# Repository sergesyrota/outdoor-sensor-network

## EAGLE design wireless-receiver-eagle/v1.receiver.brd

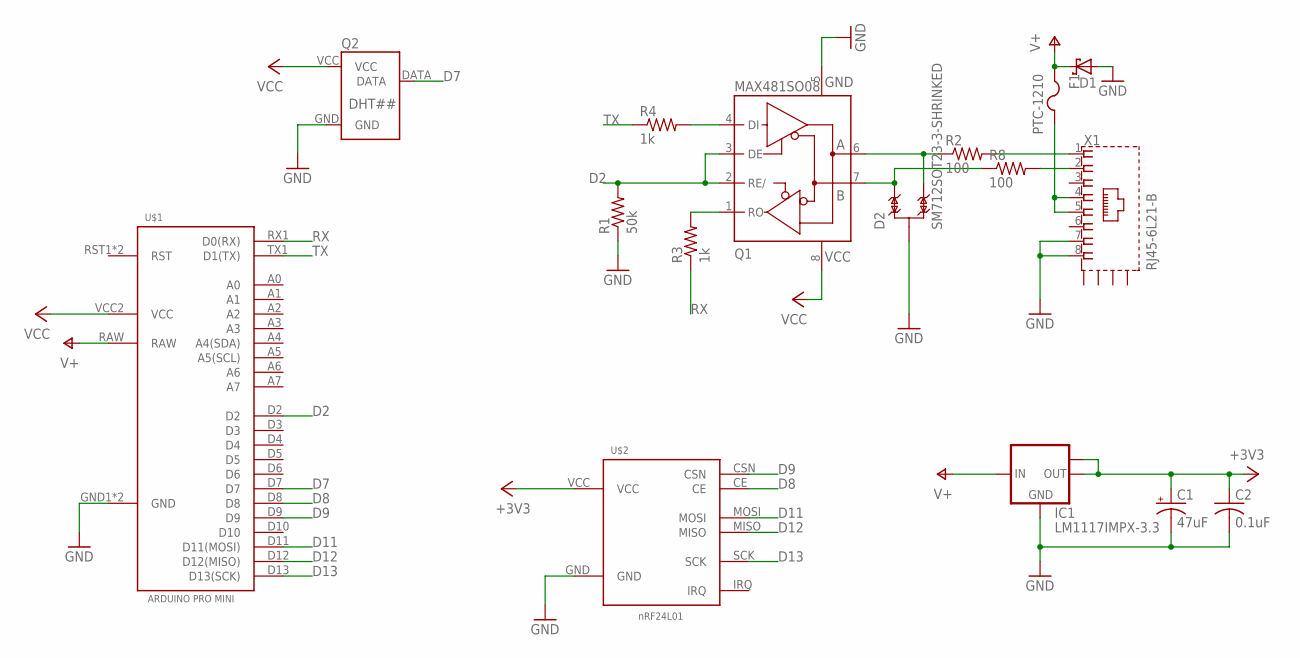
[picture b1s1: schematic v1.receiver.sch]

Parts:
C1: 47uF; E2,5-5
C2: 0.1uF; C0603
D1: SCHOTTKY-DIODESMC; SMC
D2: SM712SOT23-3-SHRINKED; SOT23-3-SHRINKED
F1: PTC-1210; 1210
IC1: LM1117IMPX-3.3; SOT223
Q1: MAX481SO08; SO08
Q2: DHT##; CONNECTOR-4-PIN-0.1
R1: 50k; R0603
R2, R8: 100; R0603
R3, R4: 1k; R0603
U$1: ARDUINO-PRO-MININO-ICSP; ARDUINO-PRO-MINI-NO-ICSP
U$2: NRF24L01MODULE; NRF24L01-MODULE
X1: RJ45-6L21-B; RJ45-SHIELD1

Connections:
+3V3: C1.+, C2.1, IC1.2 (OUT), IC1.TAB (OUT1), U$2.VCC
D2: Q1.2 (RE/), Q1.3 (DE), R1.2, U$1.D2
D7: Q2.DATA, U$1.D7
D8: U$1.D8, U$2.CE
D9: U$1.D9, U$2.CSN
D11: U$1.D11 (D11(MOSI)), U$2.MOSI
D12: U$1.D12 (D12(MISO)), U$2.MISO
D13: U$1.D13 (D13(SCK)), U$2.SCK
GND: C1.-, C2.2, D1.A, D2.3, IC1.1 (GND), Q1.5 (GND), Q2.GND, R1.1, U$1.GND1 (GND), U$1.GND4 (GND), U$2.GND, X1.7, X1.8
unnamed: F1.2, X1.4, X1.5
unnamed: D2.2, Q1.7 (B), R8.1
unnamed: Q1.1 (RO), R3.2
unnamed: Q1.4 (DI), R4.2
unnamed: R8.2, X1.2
unnamed: R2.2, X1.1
unnamed: D2.1, Q1.6 (A), R2.1
RX: R3.1, U$1.RX1 (D0(RX))
TX: R4.1, U$1.TX1 (D1(TX))
V+: D1.C, F1.1, IC1.3 (IN), U$1.RAW
VCC: Q1.8 (+5V), Q2.VCC, U$1.VCC2 (VCC)

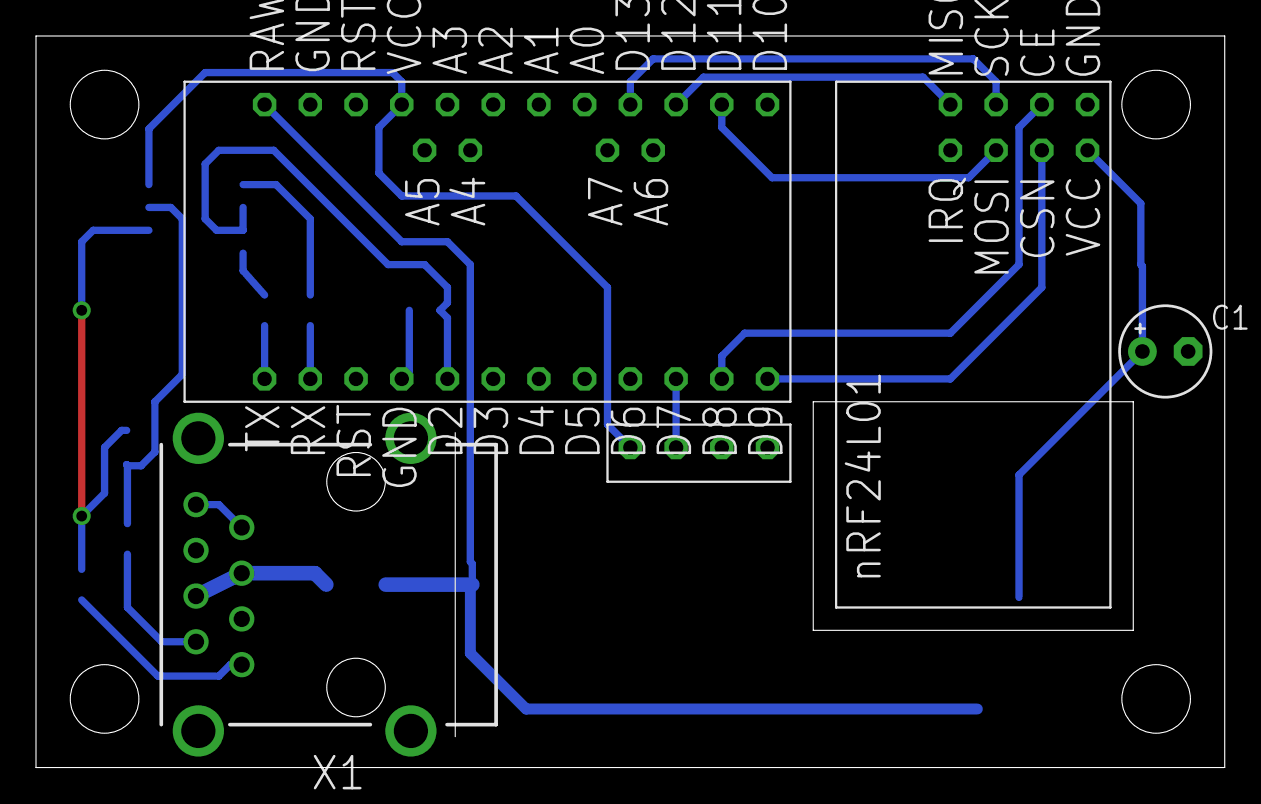
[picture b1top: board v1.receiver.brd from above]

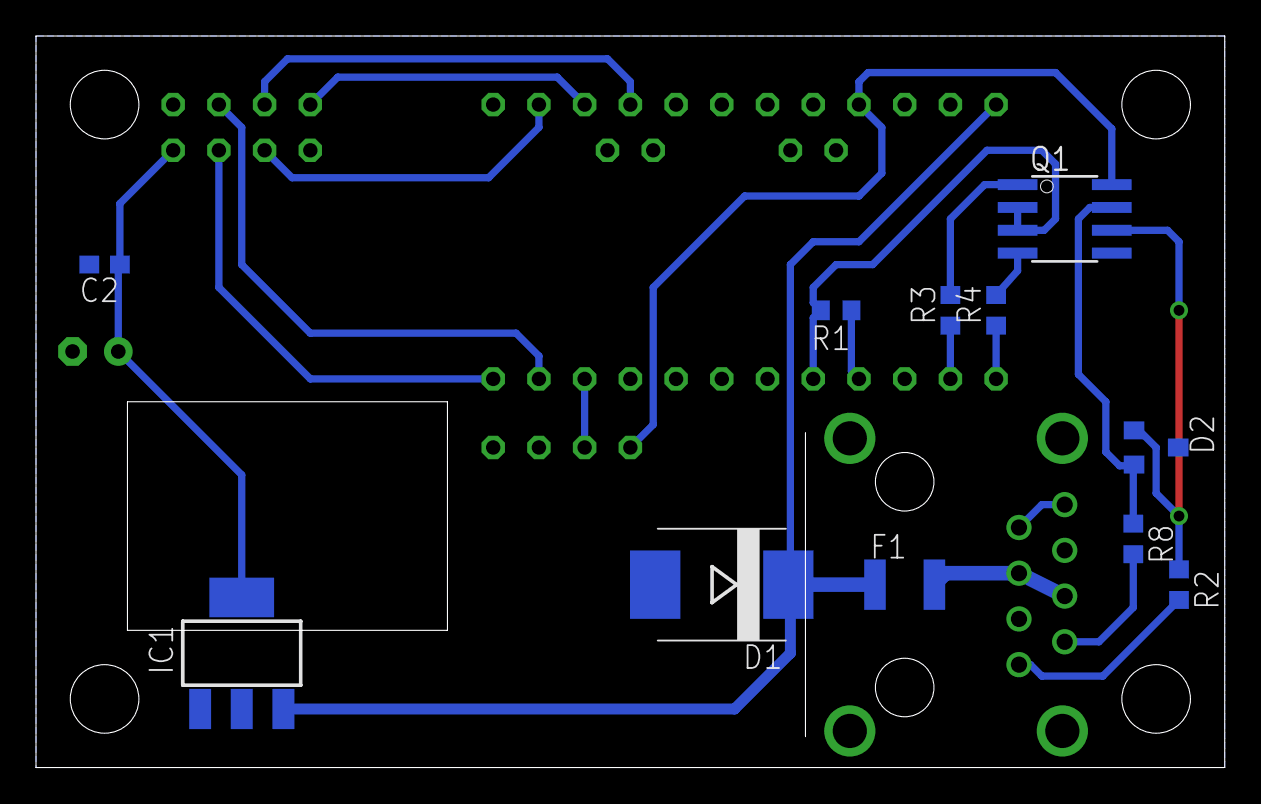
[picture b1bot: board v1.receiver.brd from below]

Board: 2 copper layers, 66.0 x 40.6 mm, 16 parts (11 on the bottom side), 20 nets.

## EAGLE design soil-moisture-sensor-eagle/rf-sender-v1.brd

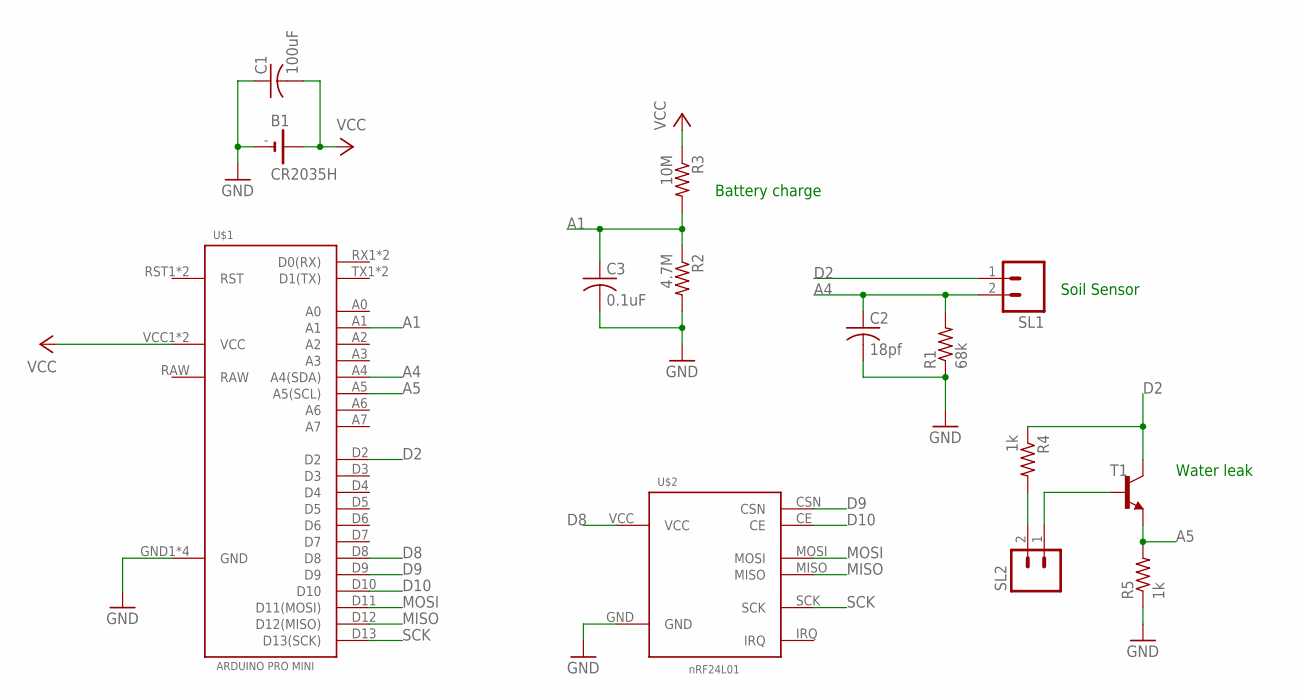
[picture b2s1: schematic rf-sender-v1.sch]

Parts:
B1: CR2035H; CR2032H
C1: 100uF; C2220K
C2: 18pf; C0805
C3: 0.1uF; C0603
R1: 68k; R0603
R2: 4.7M; R0603
R3: 10M; R0603
R4, R5: 1k; R0603
SL1, SL2: M02; 02P
T1: BC808-NPN-SOT23-BEC; SOT23-BEC
U$1: ARDUINO-PRO-MINI
U$2: NRF24L01MODULE; NRF24L01-MODULE

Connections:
A1: C3.1, R2.1, R3.2, U$1.A1
A4: C2.1, R1.2, SL1.2, U$1.A4 (A4(SDA))
A5: R5.2, T1.E, U$1.A5 (A5(SCL))
D2: R4.1, SL1.1, T1.C, U$1.D2
D8: U$1.D8, U$2.VCC
D9: U$1.D9, U$2.CSN
D10: U$1.D10, U$2.CE
GND: B1.-, C1.1, C2.2, C3.2, R1.1, R2.2, R5.1, U$1.GND1 (GND), U$1.GND2 (GND), U$1.GND3 (GND), U$1.GND4 (GND), U$2.GND
MISO: U$1.D12 (D12(MISO)), U$2.MISO
MOSI: U$1.D11 (D11(MOSI)), U$2.MOSI
unnamed: SL2.1, T1.B
unnamed: R4.2, SL2.2
RAW: U$1.RAW
SCK: U$1.D13 (D13(SCK)), U$2.SCK
VCC: B1.+, C1.2, R3.1, U$1.VCC1 (VCC), U$1.VCC2 (VCC)

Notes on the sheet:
Water leak
Battery charge
Soil Sensor

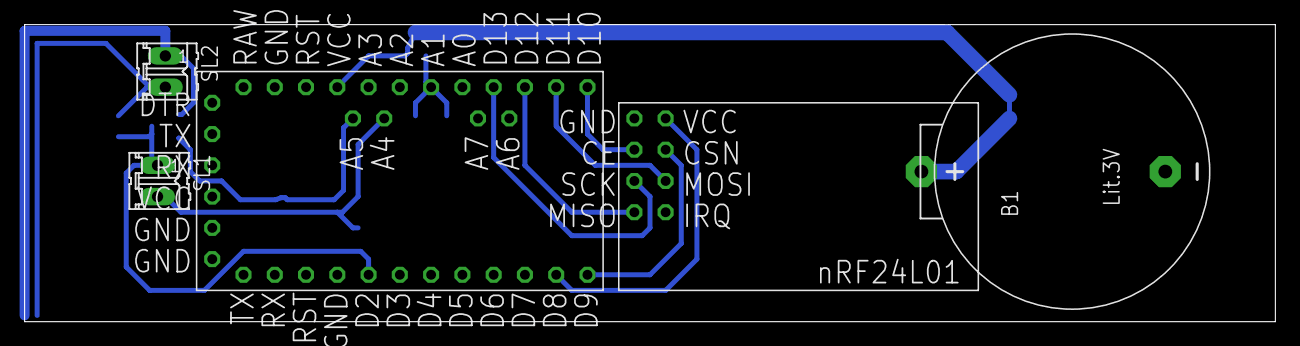
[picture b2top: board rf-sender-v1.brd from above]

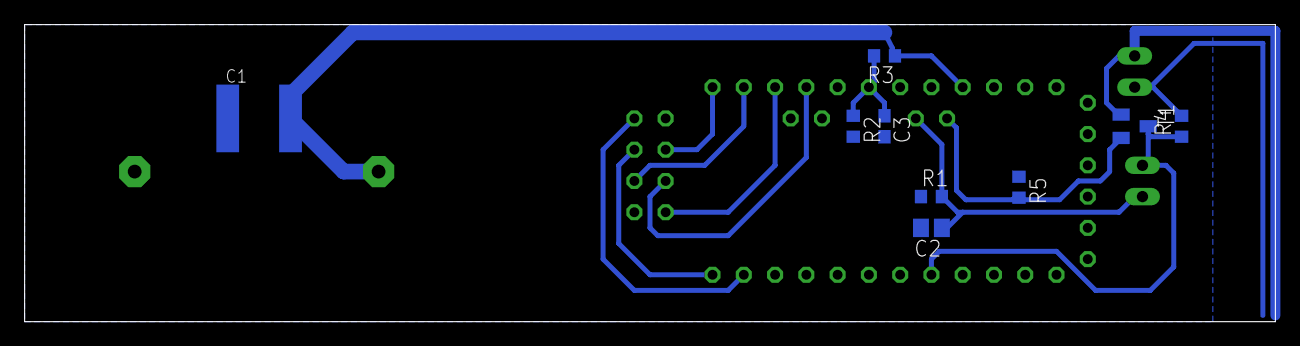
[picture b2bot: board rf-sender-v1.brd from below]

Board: 2 copper layers, 101.6 x 24.1 mm, 14 parts (9 on the bottom side), 14 nets.

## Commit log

2015-04-26 Adding wireless receiver code
2015-04-26 Added soil moisture sketch
2015-04-26 Added Eagle projects for moisture probe and outdoor receiver
